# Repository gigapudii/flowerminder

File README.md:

# Flowerminder
This gadget helps remind you to water your plants with a blinking LED-light.

## WHY
For the past few years I have gathered a larger amount of plants in my house. However, I often struggle to keep them alive due to my forgetfulness and everyday life coming inbetween. In order to keep them healthy, I decided to initiate this project which I am sure many of you are in need of as well. With an LED-light blinking on a set day, neglect can simply be avoided.

## HOW
The solution to this is the Flowerminder. It allows you to put a reminder for up to 7 days, and blinks until you have noticed the plant and hit reset. Its small, compact, and simple design is easy to use and is visible from a distance as well.

For the Flowerminder, you will need an Attiny85, along with a potentiometer (rotary potentiometer COM-09288), coin cell battery (CR2032), a LED-light (5mm), and a button (6mm tactile switch) to reset your settings. 

To design the board, Eagle CAD was used. The goal was to make it as small as possible so it wouldn't be too chunky. The holes in the board are optional, but the idea was to 3D-design a case for it that would have screws holding it in place. 

## Components
* 1x [Flowerminder board](https://www.pcbway.com/project/shareproject/Flowerminder.html)
* 1x [3D-printed case](https://www.tinkercad.com/things/kMWTQKFdEJA) 
* 1x Attiny85
* 1x Coin cell battery CR2032
* 1x Coin cell battery holder
* 1x Rotary potentiometer COM-09288
* 1x 5mm LED-light
* 1x 6mm tactile switch button
* 2x Resistor (one for the LED 220kOhm, and one for the button 10kOhm)

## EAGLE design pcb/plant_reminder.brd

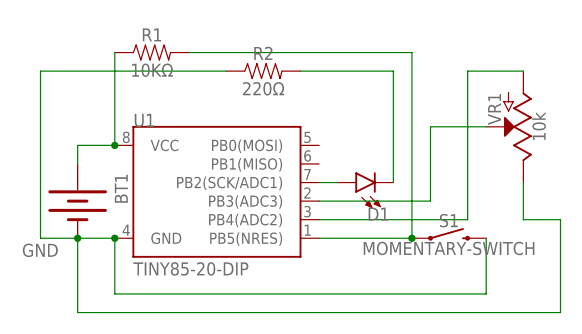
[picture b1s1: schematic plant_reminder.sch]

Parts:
BT1: BATTERYFOB; BATTERY_20MM_PTH_COMPACT
D1: LED5MM-KIT; LED_5MM-KIT
R1: 10KΩ; AXIAL-0.3
R2: 220Ω; AXIAL-0.3
S1: MOMENTARY-SWITCH; TACTILE_SWITCH_PTH_6.0MM
U1: TINY85-20-DIP; DIP08_MCU
VR1: 10k; POT-PTH-ALPS-KIT

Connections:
GND: BT1.2 (-), R2.P$1 (1), S1.3 (2), U1.4 (GND), VR1.P$1 (E)
unnamed: R1.P$2 (2), S1.1, U1.1 (PB5(NRES))
unnamed: D1.A, U1.7 (PB2(SCK/ADC1))
unnamed: D1.K (C), R2.P$2 (2)
unnamed: U1.2 (PB3(ADC3)), VR1.P$2 (S)
unnamed: U1.3 (PB4(ADC2)), VR1.P$3 (A)
VCC: BT1.1 (+), R1.P$1 (1), U1.8 (VCC)

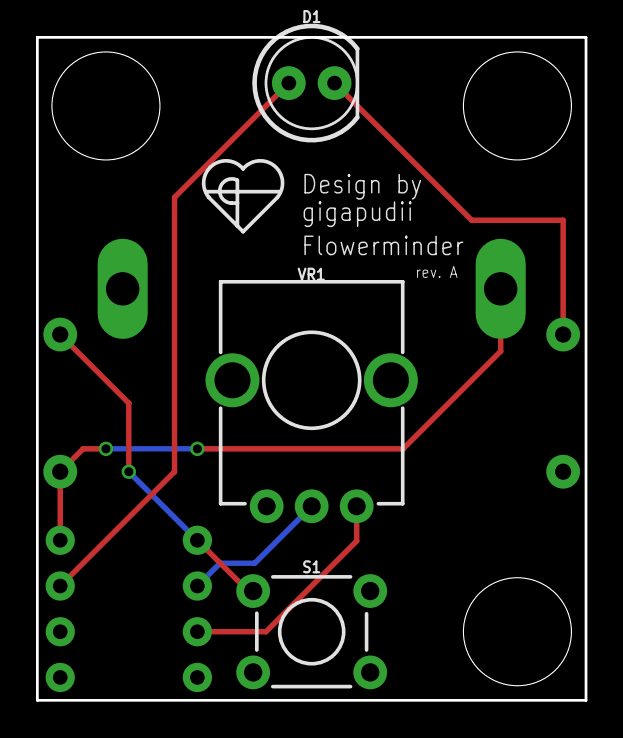
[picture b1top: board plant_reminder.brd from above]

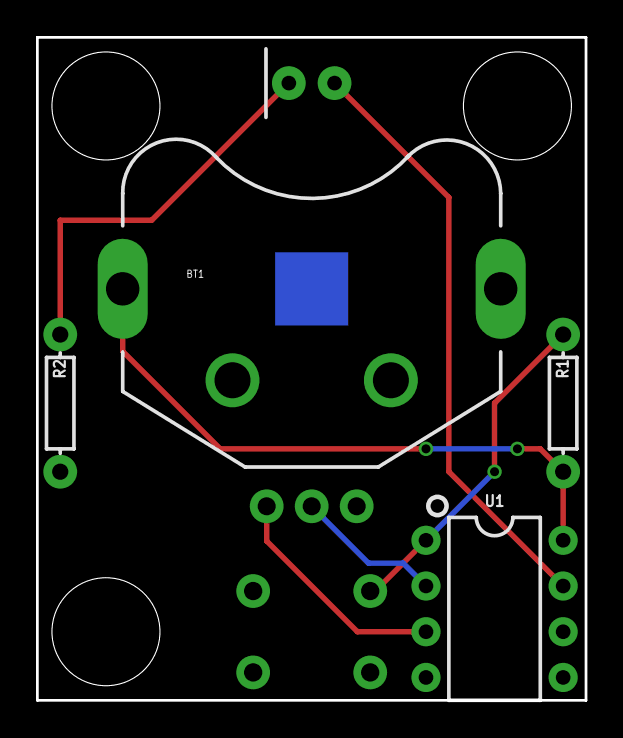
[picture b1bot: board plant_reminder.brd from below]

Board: 2 copper layers, 30.5 x 36.8 mm, 7 parts (4 on the bottom side), 7 nets.

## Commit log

2019-06-20 Add FlowerMinder initial sketch
    This sketch contains stubs of the functionality needed
    for the FlowerMinder for @gigapudii to implement and
    create the business logic.
2019-06-20 Disabled ADC and reading pot value
2019-06-24 Added deep sleep for different time periods
2019-06-26 Added amount of days and created loops
2019-06-26 Added the flowerminder pcb design
2019-06-26 Added resistor values

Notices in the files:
parts and their libraries:
SparkFun-Retired: Licensing: Creative Commons ShareAlike 4.0 International - https://creativecommons.org/licenses/by-sa/4.0
